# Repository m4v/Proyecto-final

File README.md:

# Proyecto Final - Cátedra de Ingeniería Electrónica - 2016

El objetivo de este proyecto es diseñar un sistema de control digital para un horno de prótesis dentales. 

## Contenido del repositorio

* firmware/ - Directorio con el programa del horno.
  * horno/ - Código fuente específico del horno.
  * lpc_board_nxp_lpcxpresso_1769/ - Biblioteca de la placa LPCxpresso 1769.
  * lpc_chip_175x_6x/ - Biblioteca del microcontrolador LPC1769.
  * periph_*/ - ejemplos de LPCOpen.
* kicad/ - Archivos del esquemático y PCB
  * datasheet/ - documentación de los integrados utilizados.
  * notas de aplicaciones/ - documentación sobre temas relevantes al proyecto.
  * documentación/ - archivos del horno en formato .pdf. Ej. esquemáticos
  * pcb/ - pdfs de las capas del circuito impreso.
* mediciones/ - Archivos .csv con los resultados de mediciones hechas.
  * graficos/ - Gráficos de las mediciones hechas.
  * NOTAS.txt - información sobre algunas mediciones.
* octave/ - scripts de Octave
* matlab/ - archivos de simulink y del identificador de sistemas.

## Autores
 * Gastón Riera
 * Elián Hanisch
 * Rodrigo Oliver

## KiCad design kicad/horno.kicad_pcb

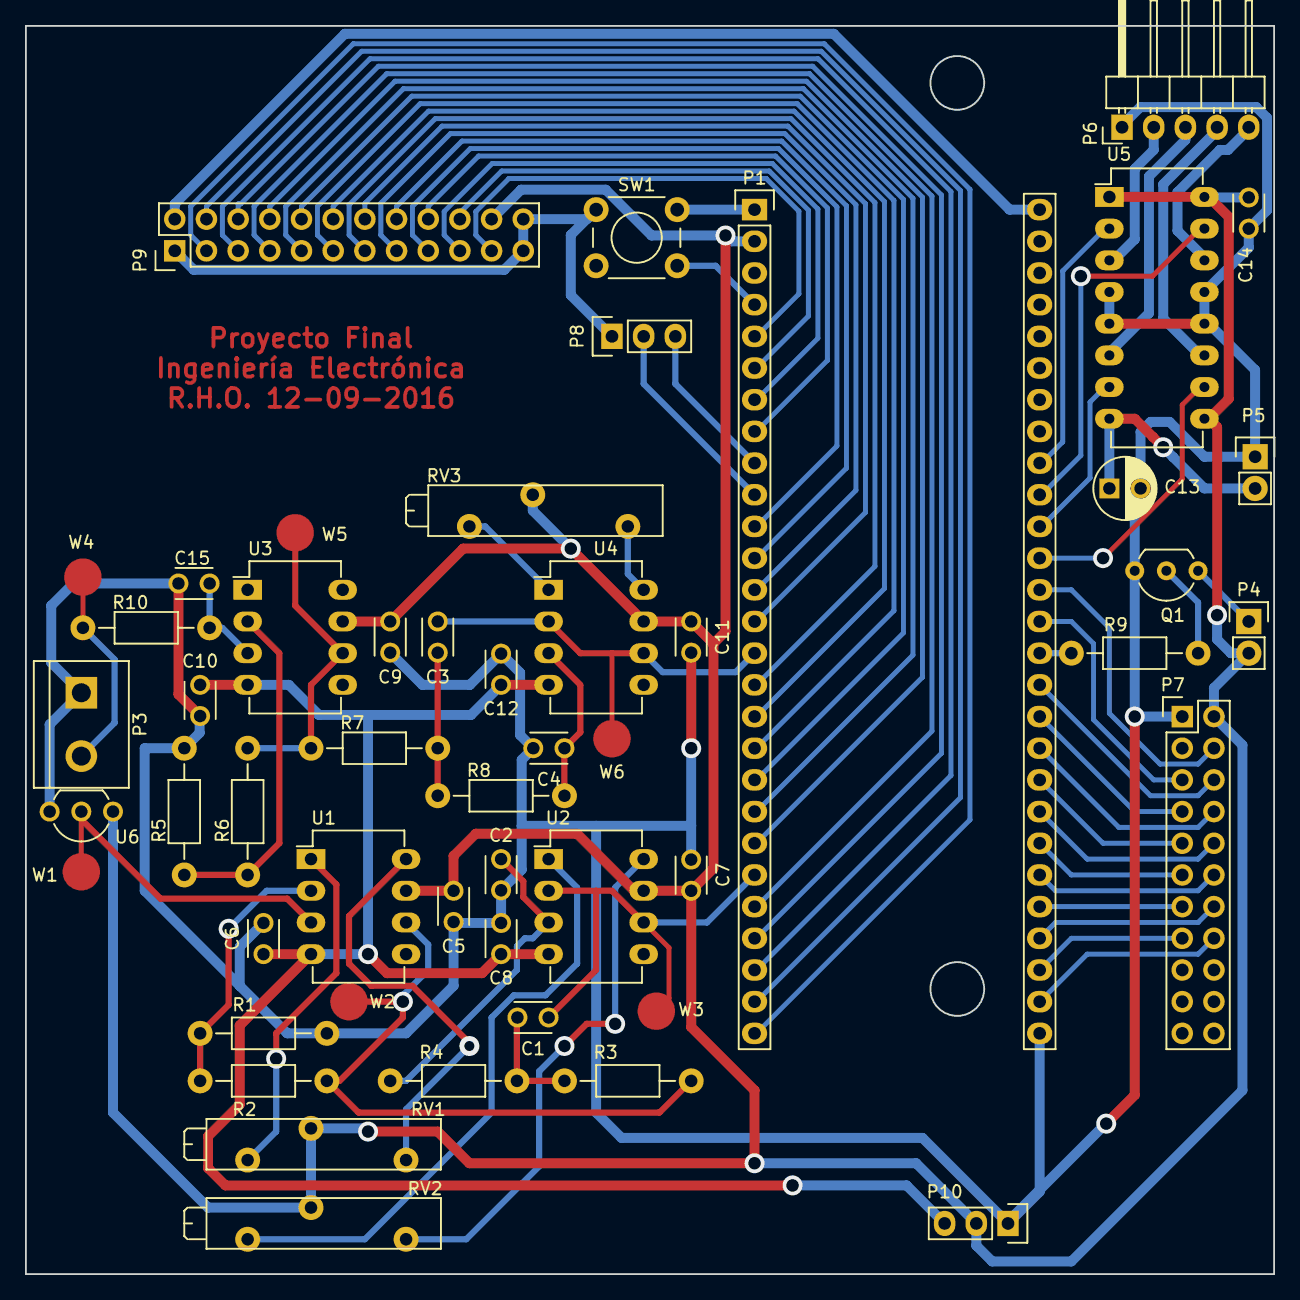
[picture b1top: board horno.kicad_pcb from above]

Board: 2 copper layers, 100.1 x 100.1 mm, 51 parts (0 on the bottom side), 71 nets.

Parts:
C1, C2, C3, C4: 220nF; C_Disc_D3_P2.5
C5, C7, C9, C11, C14: 0,1uF; C_Disc_D3_P2.5
C6, C8, C10, C12: 0.1uF; C_Disc_D3_P2.5
C13: 1uF; C_Radial_D5_L6_P2.5
C15: C; C_Disc_D3_P2.5
P1: LPC1769; Pin_Header_LPCXpresso_LPC1769
P3: Termocupla; bornier2
P4: TRIAC; Pin_Header_Straight_1x02
P5: 24V; Pin_Header_Straight_1x02
P6: Motor; Pin_Header_Angled_1x05
P7: Pantalla; Pin_Header_Straight_2x11
P8: UART; Pin_Header_Straight_1x03
P9: GPIO; Pin_Header_Straight_2x12
P10: Alimentación; Pin_Header_Straight_1x03
Q1: BC547; TO-92_Inline_Wide
R1: 10k; Resistor_Horizontal_RM10mm
R2, R3, R7: 56k; Resistor_Horizontal_RM10mm
R4, R8: 330k; Resistor_Horizontal_RM10mm
R5: 1,5k; Resistor_Horizontal_RM10mm
R6: 120k; Resistor_Horizontal_RM10mm
R9, R10: R; Resistor_Horizontal_RM10mm
RV1, RV2, RV3: POT; Potentiometer_Bourns_3005_Angular_ScrewFront
SW1: RST; SW_PUSH_6mm
U1, U2, U4: OP07; DIP-8_W7.62mm_LongPads
U3: LTC1050; DIP-8_W7.62mm_LongPads
U5: L293D; DIP-16_W7.62mm_LongPads
U6: LM35; TO-92_Inline_Wide
W1: Lm1; Measurement_Point_Round-SMD-Pad_Big
W2: Lm2; Measurement_Point_Round-SMD-Pad_Big
W3: Lm3; Measurement_Point_Round-SMD-Pad_Big
W4: Th1; Measurement_Point_Round-SMD-Pad_Big
W5: Th2; Measurement_Point_Round-SMD-Pad_Big
W6: Th3; Measurement_Point_Round-SMD-Pad_Big

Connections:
+3V3: P1.28, P9.2
+5V: C5.1, C7.1, C9.1, C11.1, C14.1, P1.2, P4.2, P7.2, P9.22, P10.2, RV1.2, RV2.2, RV3.2, U1.7, U2.7, U3.7, U4.7, U5.1, U5.9, U5.16, U6.1
+24V: C13.1, P5.2, U5.8
-5V: C6.1, C8.1, C10.1, C12.1, P10.3, U1.4, U2.4, U3.4, U4.4
/LPC1769/A0: P1.43, P7.6
/LPC1769/AD_LM35: C1.1, P1.22, U2.2, U2.6, W3.1
/LPC1769/AD_TERMOCUPLA: C3.1, P1.15, U4.2, U4.6, W6.1
/LPC1769/CS: P1.52, P7.15
/LPC1769/D0: P1.44, P7.7
/LPC1769/D1: P1.45, P7.8
/LPC1769/D2: P1.46, P7.9
/LPC1769/D3: P1.47, P7.10
/LPC1769/D4: P1.48, P7.11
/LPC1769/D5: P1.49, P7.12
/LPC1769/D6: P1.50, P7.13
/LPC1769/D7: P1.51, P7.14
/LPC1769/GPIO0: P1.27, P9.3
/LPC1769/GPIO1: P1.26, P9.4
/LPC1769/GPIO2: P1.25, P9.5
/LPC1769/GPIO3: P1.24, P9.6
/LPC1769/GPIO4: P1.23, P9.7
/LPC1769/GPIO5: P1.21, P9.8
/LPC1769/GPIO6: P1.20, P9.9
/LPC1769/GPIO7: P1.19, P9.10
/LPC1769/GPIO8: P1.18, P9.11
/LPC1769/GPIO9: P1.17, P9.12
/LPC1769/GPIO10: P1.16, P9.13
/LPC1769/GPIO11: P1.14, P9.14
/LPC1769/GPIO12: P1.13, P9.15
/LPC1769/GPIO13: P1.12, P9.16
/LPC1769/GPIO14: P1.11, P9.17
/LPC1769/GPIO15: P1.8, P9.18
/LPC1769/GPIO16: P1.7, P9.19
/LPC1769/GPIO17: P1.6, P9.20
/LPC1769/GPIO18: P1.5, P9.21
/LPC1769/PWM: P1.42, R9.2
/LPC1769/RD: P1.40, P7.4
/LPC1769/RST: P1.53, P7.16
/LPC1769/S1: P1.36, U5.2
/LPC1769/S2: P1.38, U5.7
/LPC1769/S3: P1.39, U5.10
/LPC1769/S4: P1.37, U5.15
/LPC1769/WR: P1.41, P7.5
/Motor paso a paso/OUT1: P6.2, U5.3
/Motor paso a paso/OUT2: P6.3, U5.6
/Motor paso a paso/OUT3: P6.4, U5.11
/Motor paso a paso/OUT4: P6.5, U5.14
GND: C2.2, C4.2, C5.2, C6.2, C7.2, C8.2, C9.2, C10.2, C11.2, C12.2, C13.2, C14.2, C15.2, P1.54, P3.1, P5.1, P6.1, P7.1, P10.1, Q1.3, R1.2, R5.2, U5.4, U5.5, U5.12, U5.13, U6.3
GNDD: P1.1, P8.1, P9.1, P9.23, P9.24, SW1.1
unnamed: C1.2, R3.1, R4.2
unnamed: C2.1, R4.1, U2.3
unnamed: C3.2, R7.1, R8.2
unnamed: C4.1, R8.1, U4.3
unnamed: C15.1, R10.1, U3.3
unnamed: P1.4, SW1.2
unnamed: P1.9, P8.3
unnamed: P1.10, P8.2
unnamed: P3.2, R10.2, W4.1
unnamed: P4.1, Q1.1
unnamed: Q1.2, R9.1
unnamed: R1.1, R2.2, U1.2
unnamed: R2.1, R3.2, U1.6, W2.1
unnamed: R5.1, R6.2, U3.2
unnamed: R6.1, R7.2, U3.6, W5.1
unnamed: RV1.1, U1.8
unnamed: RV1.3, U1.1
unnamed: RV2.1, U2.8
unnamed: RV2.3, U2.1
unnamed: RV3.1, U4.8
unnamed: RV3.3, U4.1
unnamed: U1.3, U6.2, W1.1

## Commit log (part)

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2016-06-20 agregar .gitignore
2016-06-22 Actualizar autores
2016-06-25 Actualización readme.md
2016-07-03 mover todos los archivos del programa al directorio firmware
    Recordar mover el directorio .metadata de LPCXpresso a firmware
    y cambiar el workspace, o crear el proyecto de nuevo.
2016-07-03 Mensaje de inicio por el UART y remover el código de los botones del motor.
2016-07-04 probar mandar comandos al micro a través del UART
2016-07-04 mover blinky al directorio firmware.
2016-07-04 readme++
2016-07-13 cambios en las velocidades del ADC
    * bajar la velocidad de muestreo a 1 muestra por 1ms
    * bajar la velocidad de conversión de 200kS a 1,4kS
    * aumentar la cantidad de muestras de 800 a 1000
2016-08-09 Funciones que usamos jugando con el display 16x02
2016-08-12 Creación de carpeta Otros
    También moví de lugar el archivo del 16x2
2016-08-17 seteo correcto de los pines
2016-08-23 minor edits
2016-08-27 ahora anda el display
2016-08-28 no ignorar los archivos .lib de Kicad
2016-08-28 minor updates + delay
2016-09-03 Ultimas modif
2016-09-03 solamente cambiar 8 bits del puerto 2 cuando se escriben datos
2016-09-03 sacar el bucle infinito de Display_Init.
    En lugar de eso, ejecutar Display_Init cada 5 seg desde el main.
2016-09-08 Así anda
    Con estos cambios anda con el display de Pablo.
    - Borra el 1er layer
    - Escribe
2016-09-11 circuito y pcb terminado.
2016-09-12 últimas modificaciones al impreso.
2016-09-15 minor updates
2016-09-16 Algunas cosas de rodri
2016-09-19 minor update
2016-09-20 archivos del BOM del proyecto
2016-09-21 Dejé que se dibuje un rectángulo en la parte inferior del display. Mejora de la legibilidad del código.
2016-09-21 renombrar Display_Init a Horno_Display_Init y llamarlo desde Horno_Init
    Agregar en el main un llamado a Horno_Display_Test.
2016-09-22 renombrar algunos comandos así son más consistentes entre sí
    CSRW => CSR_WRITE
    CSRR => CSR_READ
2016-09-22 hay un llamado a strlen pero no está string.h en los includes
2016-09-22 fix warning: statement with no effect
2016-09-22 LPCXpresso insiste en cambiar los .cproject de los ejemplos...
2016-09-22 habilitar el código del ADC nuevamente
2016-09-22 más cambios en .cproject
2016-09-28 mejorar el script, agregar un guardado de un registro
2016-09-30 mediciones, graficos y scripts de gnuplot
    * archivos .csv
    datos de las mediciones
    * archivos .gp
    scripts de gnuplot
2016-10-01 última medición del horno
2016-10-01 graficos de los ajustes
2016-10-01 usar el símbolo de tau en lugar de "tau" en los gráficos
2016-10-03 promediar muestras durante un segundo
2016-10-03 mejora del script para hacer capturas
2016-10-04 actualizar el script para que grafique los 2 AD
2016-10-07 actualizar gráficos
2016-10-07 meter algunas variables estáticas dentro de un struct
2016-10-08 script para hacer el ajuste de la curva de enfriamiento
2016-10-12 script para simular la planta y pid
2016-10-22 drivers del pwm
2016-10-22 Comentarios de funciones y curva de trabajo estática
    1- Creada función que grafica la curva de trabajo estática.
    2- Creados comentarios breves describiendo qué hace cada función
2016-10-22 Agregado Funcion: static_curve
    Hace la curva estática. :)
2016-10-22 Upgrade de static_curve a static_curve_wsqare + limpieza de tests viejos
    1- Agregado del rectángulo a la función de la curva estática
    2- Borrado de las cosas viejas y tests ya obsoletos
2016-10-22 Creada una función que mueve la flechita a lo largo de la curva estática.
2016-10-22 Creada la función: Put_string_waddr. Usando Put_string y Set_text_position.
2016-10-22 Funcion que testea los numeros grandes: Num_grandes_test y los va imprimiendo y borrando.
2016-10-22 Creados todos los numeros de la función Put_Number. Testeados que anden en los 10 espacios del display.
2016-10-22 test del display dentro del while de horno.c
2016-10-22 me olvidé borrar los archivos
2016-10-22 Actualizar los pines del diplay a los del PCB
2016-10-22 cambios de los cprojects
2016-10-22 adc.h y adc.c : linealizacion de termocupla y lm35. Mas adelante sera todo respecto a adc
    teclado.h y teclado.c : manejo de teclado
2016-10-22 codigo que falta para el teclado
2016-10-23 sacar estos TODO
2016-10-23 mejora del PWM
    Cuando se desactiva el PWM ahora se asegura que no quede en alto la salida.
2016-10-23 Primer fila del teclado funcionando
2016-10-23 Borrado de funciones de numeros grandes que no usamos más. También limpieza de cosas comentadas que estaban de más.
2016-10-24 teclado andando
2016-10-24 encabezado para el pid y lazo de control
2016-10-24 Entra el sistickhandler() que viene del horno.c
2016-10-24 van de nuevo porque comente unas cosas y no los habia guardado antes de comietear
2016-10-24 renombrar telcado.c => teclado.c
2016-10-24 ordenar líneas
2016-10-24 Mejora la función que borra los números. Edición sugerida por Elián.
2016-10-25 mejora del ingreso de datos
    Uno presiona # para ingresar el dato en memoria y posteriormente usa C o D para configurar el ciclo de trabajo o periodo del PWM con el dato ingresado.
2016-10-25 scriptsito de octave para convertir la imagen de la flecha.
2016-10-26 se cambio el nombre de los valores de temperatura en grados
2016-10-26 se borro el codigo comentado
2016-10-26 Correcta configuración de las funciones que ponen datos.
2016-10-26 Limpieza de código, comentarios de más.
2016-10-26 corregir error de linkeo
2016-10-26 Configuración para mostrar datos del PWM e ingresos por teclado
2016-10-26 Creada la sección del grado centígrado dentro de la estructura. Puesto para que se muestre en el bucle infinito
2016-10-27 corrección en las constantes del AD
2016-10-27 borrada un comentario que está de mas.
2016-10-27 Dentro del display_test usamos la funcion recien creada para mostrar los datos del pwm. También algunos commentarios menos.
2016-10-27 Mejorada la función Horno_grafico_datos_pwm, para que borre los campos antes de escribirlos
2016-10-28 Descomentar el código del UART
2016-10-29 separar Horno_grafico_datos_pwm en funciones más discretas
2016-10-29 refactorizar el bucle principal.
    Se elimina buena parte del código para muestrear el AD que ya cumplió su función.
2016-10-29 Cambiamos el apagado del PWM para que no use una interrupción
    en lugar de esperar a que el PWM pase a bajo, cambiamos el puerto a GPIO con R de pull-down.
2016-10-29 Código para prender y apagar el PWM desde el UART
2016-10-29 grafico.h tiene que ir a la carpeta de includes
2016-10-29 poner las constantes de polinomio como static const
    static para limitarlas solo a adc.c y const porque son constantes
2016-10-29 th_cantidad y lm_cantidad son siempre iguales, usar una sola.
    No vamos a usar un promedio distinto para el LM35 y la termocupla.
2016-10-29 ya somos grandes y no necesitamos tener los ejemplos en el proyecto.
2016-10-30 el periodo de muestreo del PI es el mismo del AD promediado
2016-10-30 pasar el dato del ciclo de trabajo con más precisión
2016-10-30 Agregar comando para abrir el lazo por si hace falta
2016-10-30 esta variable tiene que ser volatile
    Sin el volatile, si uno compila en modo Release el optimizador la elimina.
2016-10-30 faltó esto. Si hay errores, continuar
2016-10-31 Acomodo mensaje que se muestra por la tecla A
2016-10-31 Borradas funciones que trabajaban sobre una flecha que no usamos más.
2016-10-31 Leyenda "TEMPERATURA: " se pone con la función de los números.
2016-10-31 Quitadas lineas que fueron a otras funciones
2016-11-02 datos de los ensayos del PI
2016-11-02 agregar método para configurar la referencia desde el UART
2016-11-02 Quitada la condición del if Adoptada la sugerencia de elián, usar horno_pwm.activo como condición.
2016-11-02 Funcion seteo referencia con teclado. Con la tecla B seteamos la referencia. Habría que hacer una función aparte, esto es sólo temporal.
2016-11-03 Función que pone el tiempo restante. Lo hace en numeros grandes y en formato HH:MM.
2016-11-03 Letras E y R para condición de ERROR
2016-11-03 Bitmaps letras + funciones. Mejorada funcion de tiempo, pone condición de error. También creada función FIN.
2016-11-04 Borrada cosas viejas de la flecha.
2016-11-04 activar PI por teclado y actulizar ciclo de trabajo en el display
2016-11-04 Función flecha andando.
2016-11-04 Comentarios y reordenada de las funciones
2016-11-06 fines de carrera detienen el motor.
2016-11-06 funcion borrar flecha en posición
2016-11-06 Mejora de la función que pone la hora.
2016-11-09 implementación de 2 PI, uno para el secado y otro para la cocción.
2016-11-09 Estas líneas son redundantes.
    en cada paso solo cambian 2 pines de estado.
2016-11-09 cometarios++
2016-11-09 Test de la flechita con estados. Camiando según un tiempo.
2016-11-10 nuevos valores para el PI
2016-11-10 Mejora curva+recuadro+cómo recorre la flecha
2016-11-11 Que no se imprima lo del C. Trabajo
2016-11-11 define entre paréntesis por las dudas
2016-11-11 Función de tiempo le entramos con segundos
2016-11-12 Corregir la conversión de segundos a minutos/horas
2016-11-12 en lugar de ERR, que diga 99:99
2016-11-12 Todas las mediciones que hemos hecho pero aún no comitié
2016-11-12 comando para configurar el ciclo de trabajo desde el UART
2016-11-12 Cambio posicion de numeros temperatura
2016-11-12 Modificaciones varias numeros grandes. - Movida hacia la derecha - Se borran los digitos de la temperatura
2016-11-12 Ajuste de tamaño recuadro izquierdo. - Datos mostrados - Alineaciones correspondientes. - Barra lvertical ajustada
2016-11-12 agregar los jumpers para poner la entrada del LM35 a tierra
2016-11-12 estos archivos no van
2016-11-12 fuentes en un archivo aparte
2016-11-12 Renombrado y acomodo funcion que pone los recuadros.
2016-11-12 Include para que no dé warnings.
2016-11-12 sacar cosas que quedaron superfluas
2016-11-12 Habilitar/deshabilitar carga de datos. - Cuando se inicia el programa se deshablita la carga de datos.
2016-11-13 renombrar las mediciones del programa
2016-11-13 declarar las variables en fuentes.h como const
2016-11-14 Mejora para que no se muestre la imagen.
2016-11-15 gráficos del programa de cocción
2016-11-15 comentarios+++
2016-11-16 resultados del último ensayo
2016-11-17 gráficos de las mediciones con el osciloscopio.
2016-11-17 Modificaciones varias. - Nada que cambie el funcionamiento. - Cosas de sintaxis y elegancia del codigo
2016-11-17 optimización en la función que grafica dígitos.
2016-11-18 cambio del periodo del PWM
2016-11-18 nuevo ensayo
2016-11-18 sacar estos comentarios.
2016-11-18 que el LED parpadeé cuando captura una muestra de temperatura.
2016-11-18 mover horno_estado a la estructura en horno_programa
2016-11-18 meter las variables globales de delay.c en una estructura
2016-11-18 cambio gráfico - referencia con línea punteada
2016-11-18 Revert "arreglo tentativo para los cuelgues en Horno_udelay"
    This reverts commit 310435ad88b52523e0398aa4f8ab7ab5d1a16ac1.
2016-11-21 archivos de matlab usados para sintonizar el PI
2016-11-22 mediciones del circuito del lm35 que nose porque no commitié antes.
2016-11-23 cambiar de estado en la temperatura consigna y no a 10° menos
2016-11-26 scripts para graficar mediciones
2016-11-26 algunos detalles de las mediciones
2016-11-26 PENDIENTE_MAX => PENDIENTE_CALENTAMIENTO
2016-11-26 vaya uno a saber como es que esto funcionaba sin esta funcion en el encabezado.
2016-11-26 este código no se usa
2016-11-26 Estos archivos no se usa en el proyecto
2016-11-27 agregar LED indicador del PWM.
2016-11-27 actualizar el readme del repo
2016-11-27 Comentarios ++ - brief de las funciones - Emprolijadas de algunos detalles - Cambio de display_test a display_static
2016-11-27 Agregados los Briefs de los handlers
2016-11-27 mover horno_display_static a grafico.c y renombrar apropiadamente
